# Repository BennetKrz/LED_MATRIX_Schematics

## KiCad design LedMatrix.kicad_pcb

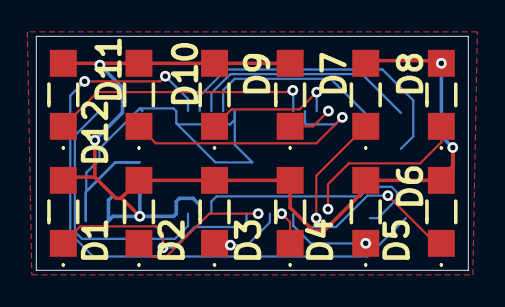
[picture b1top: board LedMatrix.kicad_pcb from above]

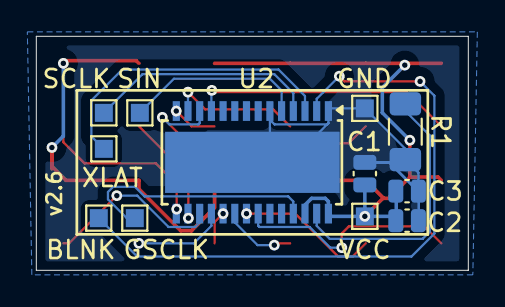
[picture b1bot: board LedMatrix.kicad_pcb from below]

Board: 4 copper layers, 24.0 x 13.0 mm, 24 parts (12 on the bottom side), 20 nets.

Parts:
BLNK: TestPoint; TestPoint_Pad_1.0x1.0mm
C1, C3: 4.7uF; C_0504_1310Metric_Pad0.83x1.28mm_HandSolder
C2: 0.1uF; C_0504_1310Metric_Pad0.83x1.28mm_HandSolder
D1, D2, D3, D4, D5, D6, D7, D8, D9, D10, D11, D12: LED; SM1206UWCIL
GND: TestPoint; TestPoint_Pad_1.0x1.0mm
GSCLK: TestPoint; TestPoint_Pad_1.0x1.0mm
R1: 2kO; R_1206_3216Metric_Pad1.30x1.75mm_HandSolder
SCLK: TestPoint; TestPoint_Pad_1.0x1.0mm
SIN: TestPoint; TestPoint_Pad_1.0x1.0mm
U2: TLC5940PWP; HTSSOP-28-1EP_4.4x9.7mm_P0.65mm_EP3.4x9.5mm_Mask2.4x6.17mm_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
VCC: TestPoint; TestPoint_Pad_1.0x1.0mm
XLAT: TestPoint; TestPoint_Pad_1.0x1.0mm

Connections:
GND: C1.2, C2.2, C3.2, GND.1, R1.1, U2.1 (GND), U2.6 (VPRG), U2.29 (PAD)
unnamed: D1.1 (K), U2.22 (OUT15)
unnamed: D2.1 (K), U2.21 (OUT14)
unnamed: D3.1 (K), U2.20 (OUT13)
unnamed: D4.1 (K), U2.19 (OUT12)
unnamed: D5.1 (K), U2.18 (OUT11)
unnamed: D6.1 (K), U2.17 (OUT10)
unnamed: D7.1 (K), U2.16 (OUT9)
unnamed: D8.1 (K), U2.15 (OUT8)
unnamed: D9.1 (K), U2.14 (OUT7)
unnamed: D10.1 (K), U2.13 (OUT6)
unnamed: D11.1 (K), U2.12 (OUT5)
unnamed: D12.1 (K), U2.11 (OUT4)
unnamed: BLNK.1, U2.2 (BLANK)
unnamed: GSCLK.1, U2.25 (GSCLK)
unnamed: R1.2, U2.27 (IREF)
unnamed: SCLK.1, U2.4 (SCLK)
unnamed: SIN.1, U2.5 (SIN)
unnamed: U2.3 (XLAT), XLAT.1
VCC: C1.1, C2.1, C3.1, D1.2 (A), D2.2 (A), D3.2 (A), D4.2 (A), D5.2 (A), D6.2 (A), D7.2 (A), D8.2 (A), D9.2 (A), D10.2 (A), D11.2 (A), D12.2 (A), U2.26 (DCPRG), U2.28 (VCC), VCC.1
